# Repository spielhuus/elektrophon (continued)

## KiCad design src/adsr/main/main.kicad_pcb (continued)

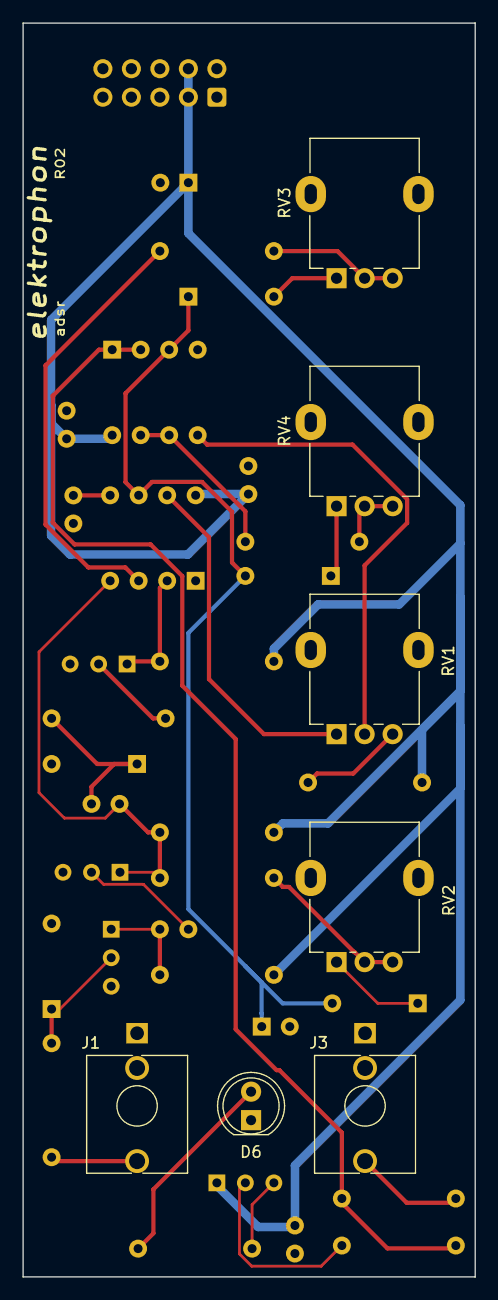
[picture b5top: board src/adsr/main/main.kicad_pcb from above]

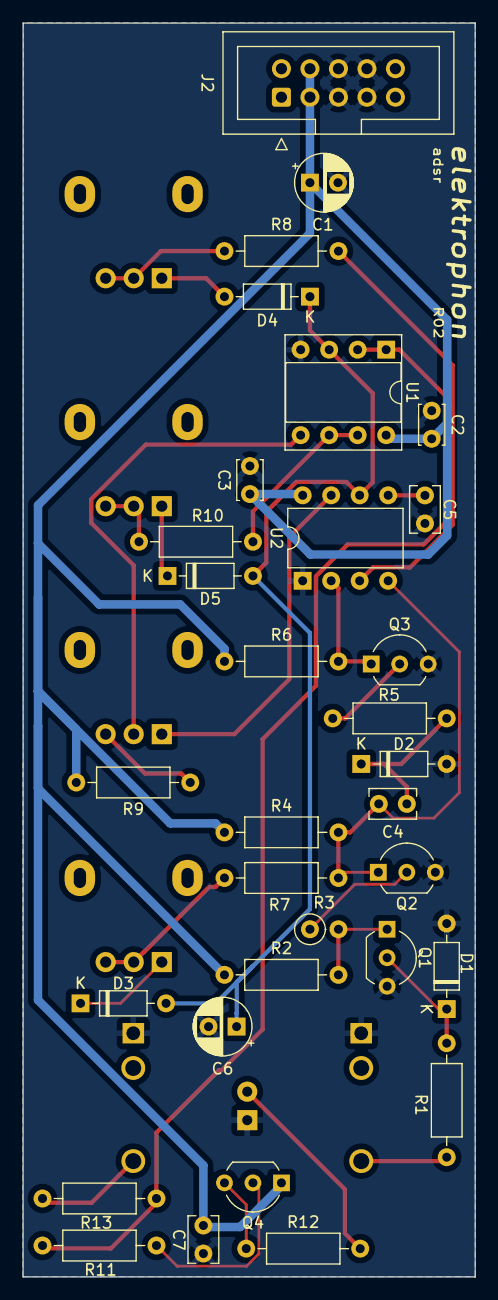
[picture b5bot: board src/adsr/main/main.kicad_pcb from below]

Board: 2 copper layers, 40.3 x 111.8 mm, 39 parts (32 on the bottom side), 28 nets.
